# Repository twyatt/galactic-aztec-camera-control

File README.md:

# About

Custom board used to activate [HackHD] cameras onboard the [Galactic Aztec] rocket. The board was designed to interface with the [Galactic Aztec RPi Add-on: Valve + Camera Control] board (rev2 or newer).

Custom EagleCAD parts on this board can be found in the [SDSU Rocket Eagle Libraries].

# Bill of Materials

| Qty | Description                             | Part Number     | Vendor  |
|:---:|-----------------------------------------|----------------:|---------|
| 1   | Jack RJ45 CAT5/CAT5e                    | [380-1046-ND]   | DigiKey |
| 1   | Header JST PH 2mm 2-pos Right Angle SMD | [455-1749-1-ND] | DigiKey |
| 1   | Header JST PH 2mm 4-pos Right Angle SMD | [455-1751-1-ND] | DigiKey |

[HackHD]: http://hackhd.com/
[Galactic Aztec]: http://rocket.sdsu.edu/rockets
[Galactic Aztec RPi Add-on: Valve + Camera Control]: https://github.com/twyatt/galactic-aztec-rpi-addon-valve-camera
[SDSU Rocket Eagle Libraries]: https://github.com/twyatt/SDSURocket-Eagle-Libraries
[380-1046-ND]: http://www.digikey.com/product-detail/en/SS-7188-NF/380-1046-ND/388308
[455-1749-1-ND]: http://www.digikey.com/product-detail/en/S2B-PH-SM4-TB(LF)(SN)/455-1749-1-ND/926846
[455-1751-1-ND]: http://www.digikey.com/product-detail/en/S4B-PH-SM4-TB(LF)(SN)/455-1751-1-ND/926848

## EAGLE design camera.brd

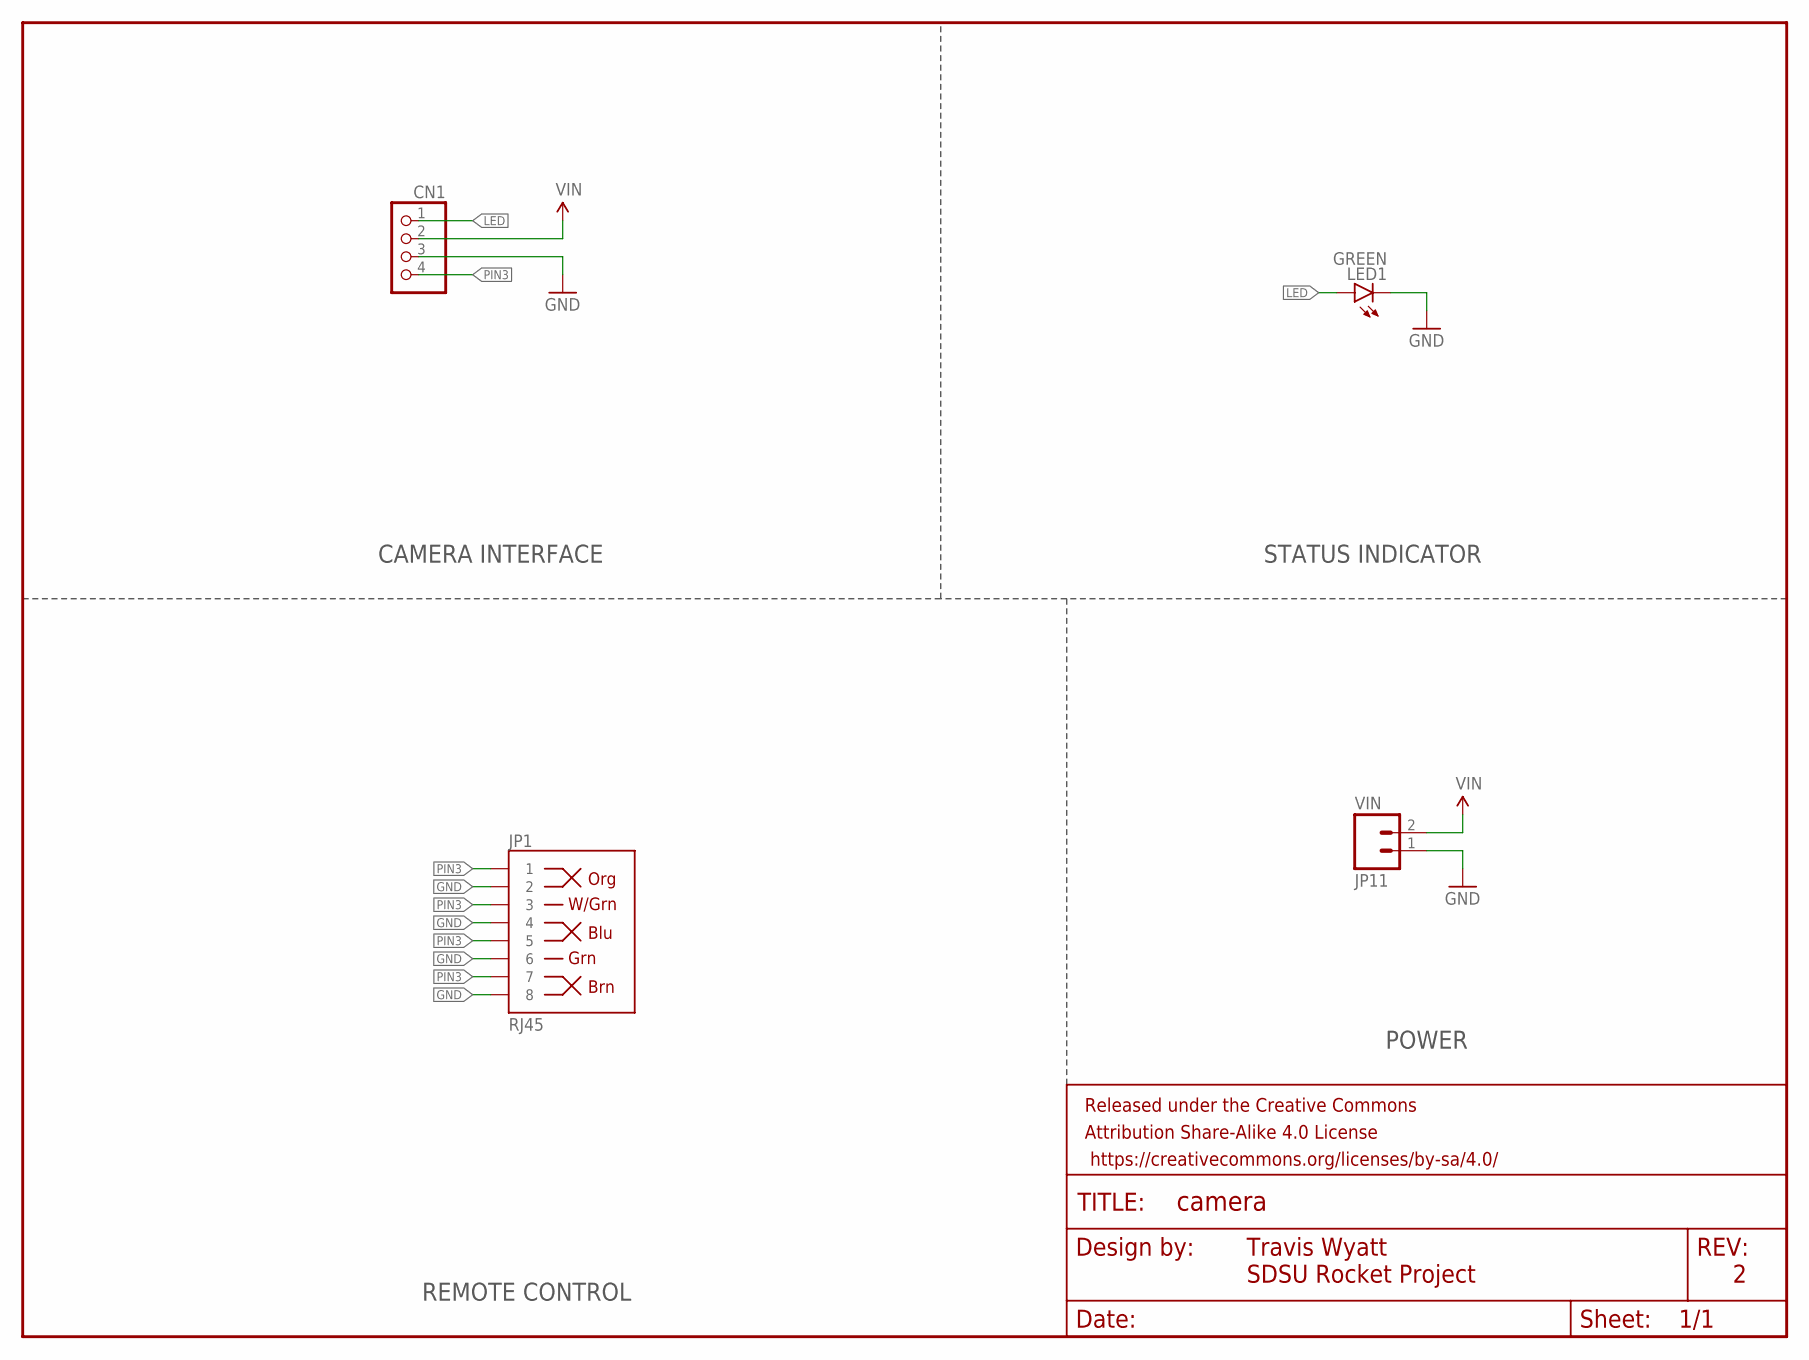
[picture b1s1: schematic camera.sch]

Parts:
CN1: JST_4PIN; JSTPH4
FRAME1: FRAME-LETTER; CREATIVE_COMMONS
JP1: RJ45; RJ45-8
JP11: VIN; JST-2-SMD
LED1: GREEN; LED-0603

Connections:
GND: CN1.3, JP1.2, JP1.4, JP1.6, JP1.8, JP11.1 (2), LED1.C
LED: CN1.1, LED1.A
PIN3: CN1.4, JP1.1, JP1.3, JP1.5, JP1.7
VIN: CN1.2, JP11.2 (1)

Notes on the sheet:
Travis Wyatt
SDSU Rocket Project
POWER
STATUS INDICATOR
CAMERA INTERFACE
REMOTE CONTROL

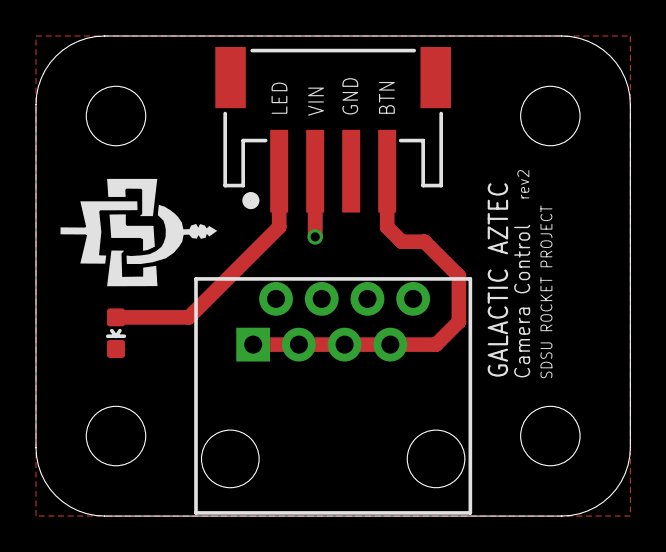
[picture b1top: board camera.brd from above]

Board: 2 copper layers, 33.0 x 26.7 mm, 9 parts (1 on the bottom side), 4 nets.

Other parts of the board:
U$1, U$2, U$3, U$4: STAND-OFF

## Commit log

2015-08-04 Significantly reduce board footprint
    Significant reduction in board footprint as the result of moving relay
    and related electronic components to the supporting Galactic Aztec RPi
    Add-on: Valve + Camera Control board.
    Components that remain on this board were replaced with SMD versions.

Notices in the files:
parts and their libraries:
SparkFun-Connectors: Licensing: Creative Commons ShareAlike 4.0 International - https://creativecommons.org/licenses/by-sa/4.0
SparkFun-Aesthetics: Released under the Creative Commons Attribution Share-Alike 4.0 License
SparkFun-Aesthetics: https://creativecommons.org/licenses/by-sa/4.0
